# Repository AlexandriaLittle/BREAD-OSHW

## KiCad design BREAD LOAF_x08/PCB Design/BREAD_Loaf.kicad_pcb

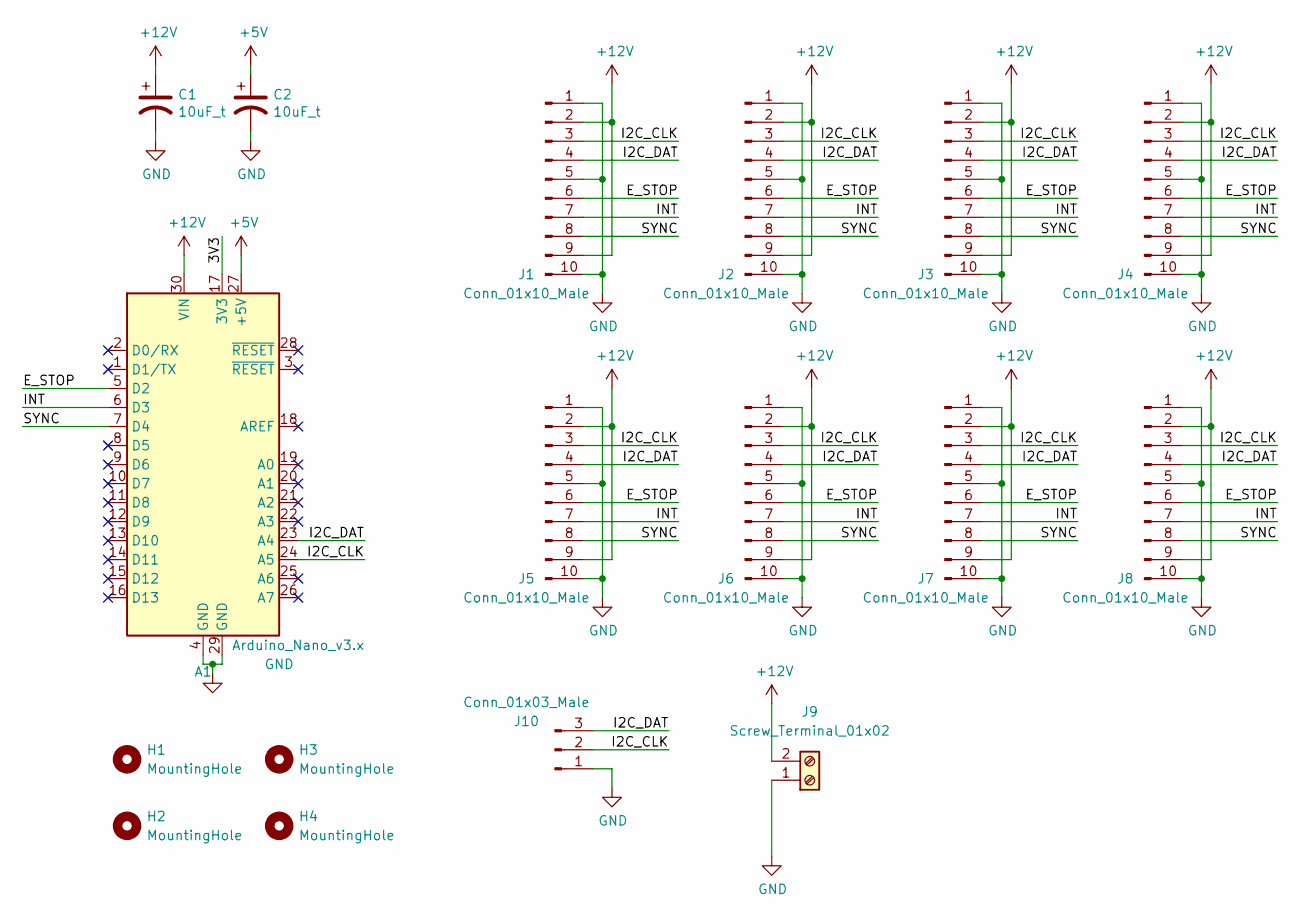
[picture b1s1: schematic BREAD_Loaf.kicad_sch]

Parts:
A1: Arduino_Nano_v3.x; Arduino_Nano
C1, C2: 10uF_t; C_1206_3216Metric_Pad1.33x1.80mm_HandSolder; Part # T491C106K025AT
H1, H2, H3, H4: MountingHole; MountingHole_3.2mm_M3_DIN965_Pad
J1, J2, J3, J4, J5, J6, J7, J8: Conn_01x10_Male; PinHeader_1x10_P2.54mm_Vertical
J9: Screw_Terminal_01x02; TerminalBlock_Phoenix_MKDS-1,5-2_1x02_P5.00mm_Horizontal
J10: Conn_01x03_Male; PinHeader_1x03_P2.54mm_Vertical

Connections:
+5V: A1.27 (+5V), C2.1
+12V: A1.30 (VIN), C1.1, J1.2, J1.9, J2.2, J2.9, J3.2, J3.9, J4.2, J4.9, J5.2, J5.9, J6.2, J6.9, J7.2, J7.9, J8.2, J8.9, J9.2
/3V3: A1.17 (3V3)
/E_STOP: A1.5 (D2), J1.6, J2.6, J3.6, J4.6, J5.6, J6.6, J7.6, J8.6
/I2C_CLK: A1.24 (A5), J1.3, J2.3, J3.3, J4.3, J5.3, J6.3, J7.3, J8.3, J10.2
/I2C_DAT: A1.23 (A4), J1.4, J2.4, J3.4, J4.4, J5.4, J6.4, J7.4, J8.4, J10.3
/INT: A1.6 (D3), J1.7, J2.7, J3.7, J4.7, J5.7, J6.7, J7.7, J8.7
/SYNC: A1.7 (D4), J1.8, J2.8, J3.8, J4.8, J5.8, J6.8, J7.8, J8.8
GND: A1.4 (GND), A1.29 (GND), C1.2, C2.2, J1.1, J1.5, J1.10, J2.1, J2.5, J2.10, J3.1, J3.5, J3.10, J4.1, J4.5, J4.10, J5.1, J5.5, J5.10, J6.1, J6.5, J6.10, J7.1, J7.5, J7.10, J8.1, J8.5, J8.10, J9.1, J10.1

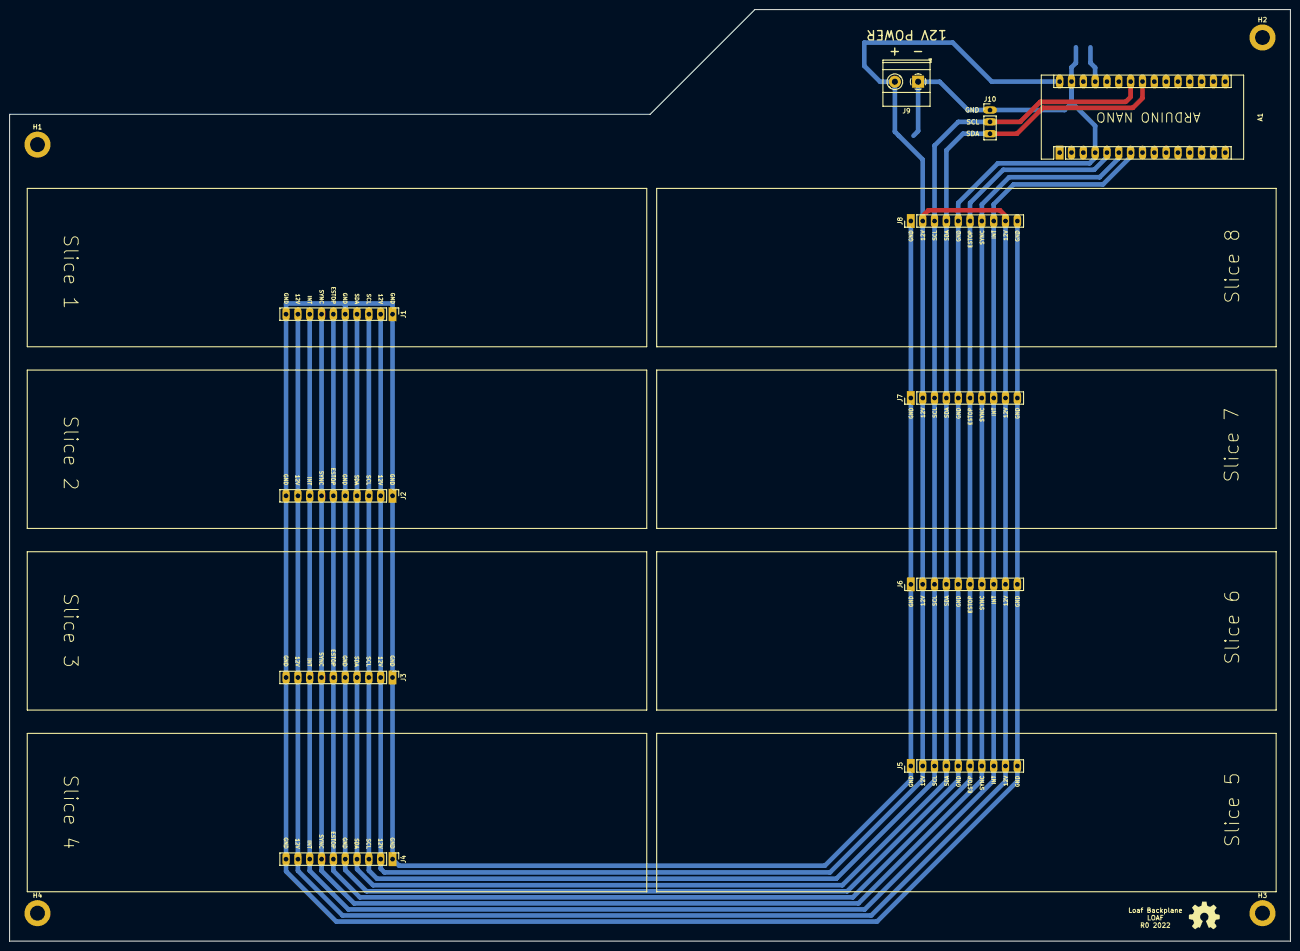
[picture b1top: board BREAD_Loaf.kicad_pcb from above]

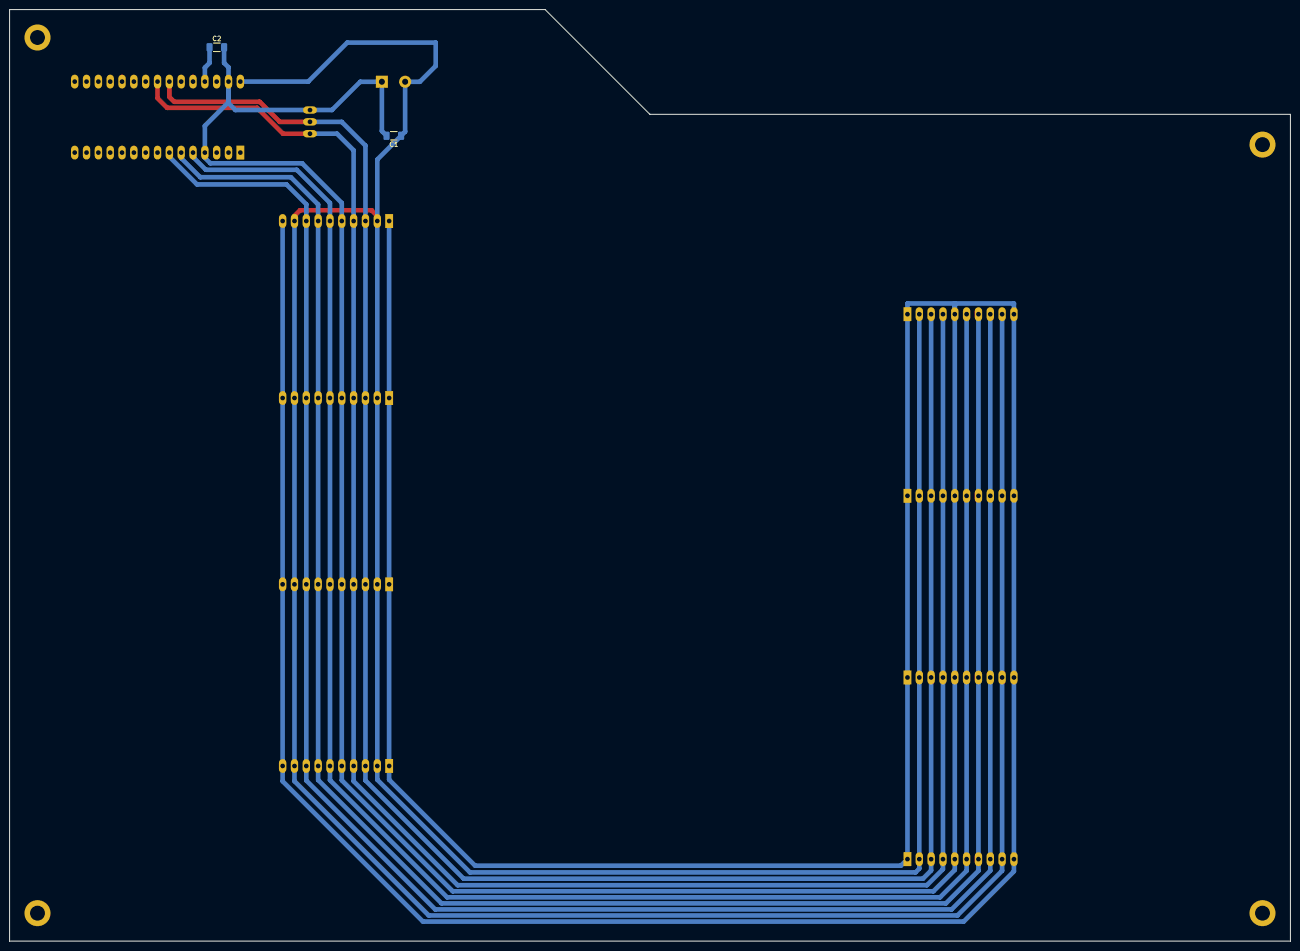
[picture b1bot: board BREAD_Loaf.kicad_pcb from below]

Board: 2 copper layers, 275.0 x 200.0 mm, 18 parts (2 on the bottom side), 8 nets.

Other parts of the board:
Logo1: Logo_Open_Hardware_Small; OSHW-Symbol_6.7x6mm_SilkScreen

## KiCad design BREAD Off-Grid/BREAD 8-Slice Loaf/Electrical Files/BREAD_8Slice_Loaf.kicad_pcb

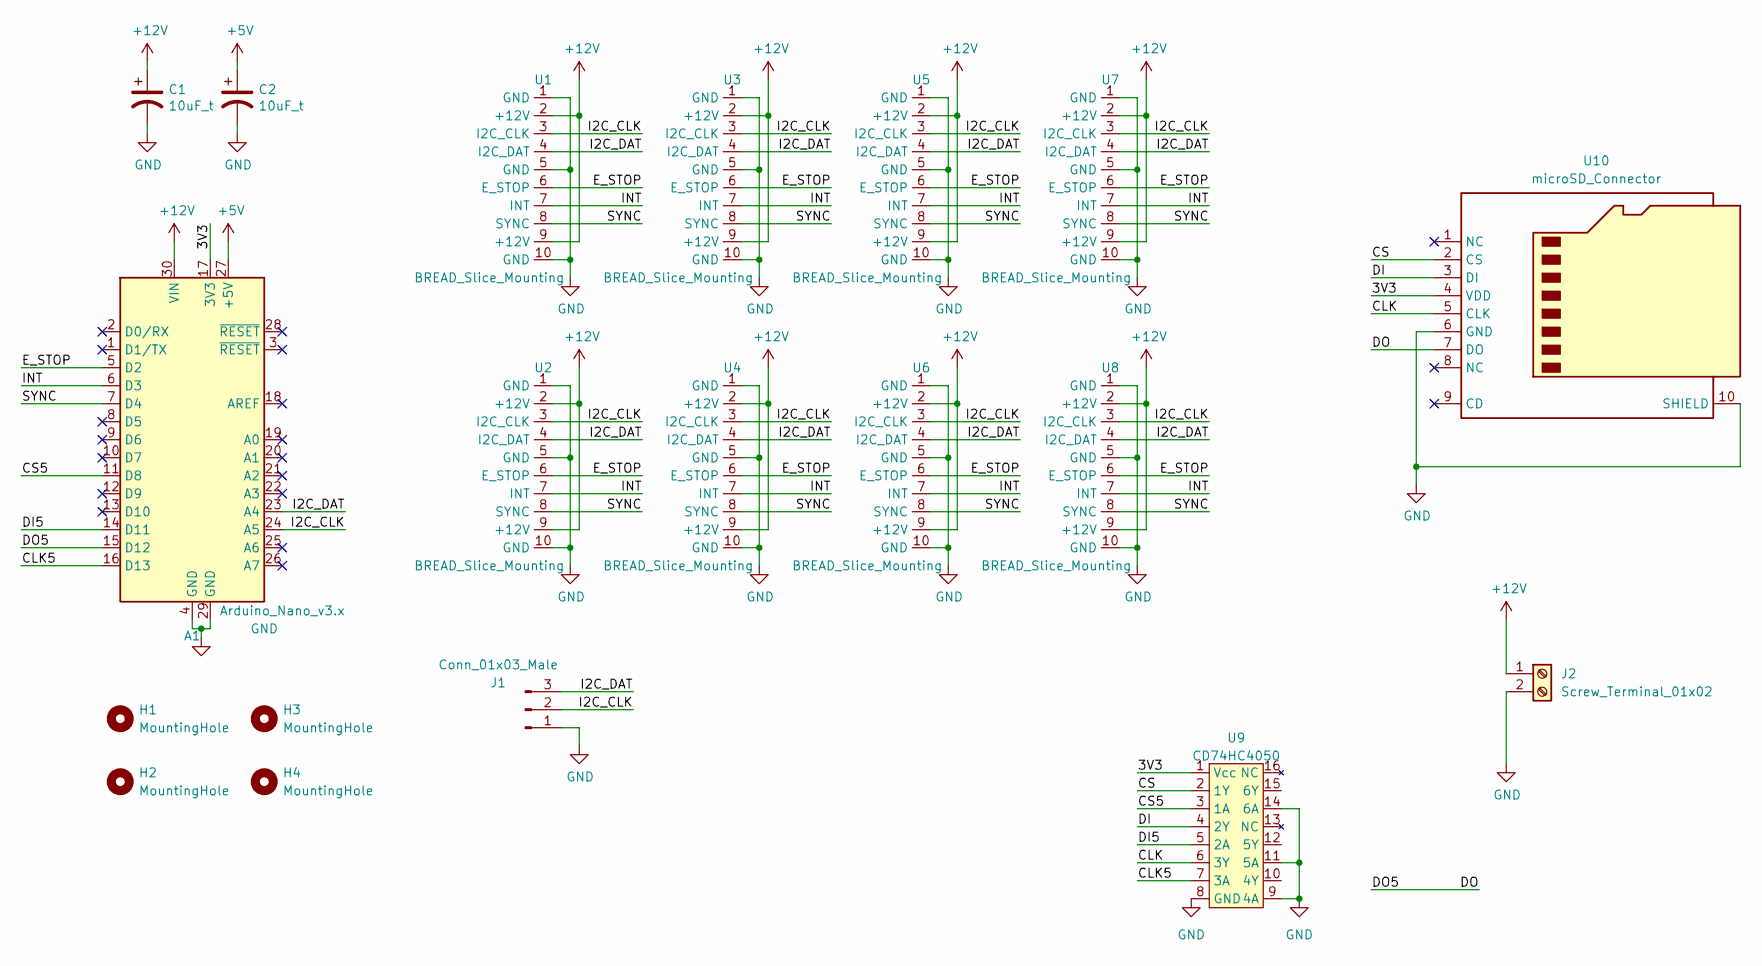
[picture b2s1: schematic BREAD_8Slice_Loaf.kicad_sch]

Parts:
A1: Arduino_Nano_v3.x; Arduino_Nano
C1, C2: 10uF_t; C_1206_3216Metric_Pad1.33x1.80mm_HandSolder; Part # T491C106K025AT
H1, H2, H3, H4: MountingHole; MountingHole_3.2mm_M3_DIN965_Pad
J1: Conn_01x03_Male; PinHeader_1x03_P2.54mm_Vertical
J2: Screw_Terminal_01x02; TerminalBlock_Phoenix_MKDS-1,5-2_1x02_P5.00mm_Horizontal
U1, U2, U3, U4, U5, U6, U7, U8: BREAD_Slice_Mounting
U9: CD74HC4050; DIP-16_W7.62mm_Socket_LongPads
U10: microSD_Connector; micro_SD_LOAF

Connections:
+5V: A1.27 (+5V), C2.1
+12V: A1.30 (VIN), C1.1, J2.1, U1.2 (+12V), U1.9 (+12V), U2.2 (+12V), U2.9 (+12V), U3.2 (+12V), U3.9 (+12V), U4.2 (+12V), U4.9 (+12V), U5.2 (+12V), U5.9 (+12V), U6.2 (+12V), U6.9 (+12V), U7.2 (+12V), U7.9 (+12V), U8.2 (+12V), U8.9 (+12V)
/3V3: A1.17 (3V3), U9.1 (Vcc), U10.4 (VDD)
/CLK: U9.6 (3Y), U10.5 (CLK)
/CLK5: A1.16 (D13), U9.7 (3A)
/CS: U9.2 (1Y), U10.2 (CS)
/CS5: A1.11 (D8), U9.3 (1A)
/DI: U9.4 (2Y), U10.3 (DI)
/DI5: A1.14 (D11), U9.5 (2A)
/DO: A1.15 (D12), U10.7 (DO)
/E_STOP: A1.5 (D2), U1.6 (E_STOP), U2.6 (E_STOP), U3.6 (E_STOP), U4.6 (E_STOP), U5.6 (E_STOP), U6.6 (E_STOP), U7.6 (E_STOP), U8.6 (E_STOP)
/I2C_CLK: A1.24 (A5), J1.2, U1.3 (I2C_CLK), U2.3 (I2C_CLK), U3.3 (I2C_CLK), U4.3 (I2C_CLK), U5.3 (I2C_CLK), U6.3 (I2C_CLK), U7.3 (I2C_CLK), U8.3 (I2C_CLK)
/I2C_DAT: A1.23 (A4), J1.3, U1.4 (I2C_DAT), U2.4 (I2C_DAT), U3.4 (I2C_DAT), U4.4 (I2C_DAT), U5.4 (I2C_DAT), U6.4 (I2C_DAT), U7.4 (I2C_DAT), U8.4 (I2C_DAT)
/INT: A1.6 (D3), U1.7 (INT), U2.7 (INT), U3.7 (INT), U4.7 (INT), U5.7 (INT), U6.7 (INT), U7.7 (INT), U8.7 (INT)
/SYNC: A1.7 (D4), U1.8 (SYNC), U2.8 (SYNC), U3.8 (SYNC), U4.8 (SYNC), U5.8 (SYNC), U6.8 (SYNC), U7.8 (SYNC), U8.8 (SYNC)
GND: A1.4 (GND), A1.29 (GND), C1.2, C2.2, J1.1, J2.2, U1.1 (GND), U1.5 (GND), U1.10 (GND), U2.1 (GND), U2.5 (GND), U2.10 (GND), U3.1 (GND), U3.5 (GND), U3.10 (GND), U4.1 (GND), U4.5 (GND), U4.10 (GND), U5.1 (GND), U5.5 (GND), U5.10 (GND), U6.1 (GND), U6.5 (GND), U6.10 (GND), U7.1 (GND), U7.5 (GND), U7.10 (GND), U8.1 (GND), U8.5 (GND), U8.10 (GND), U9.8 (GND), U9.9 (4A), U9.11 (5A), U9.14 (6A), U10.6 (GND), U10.10 (SHIELD)

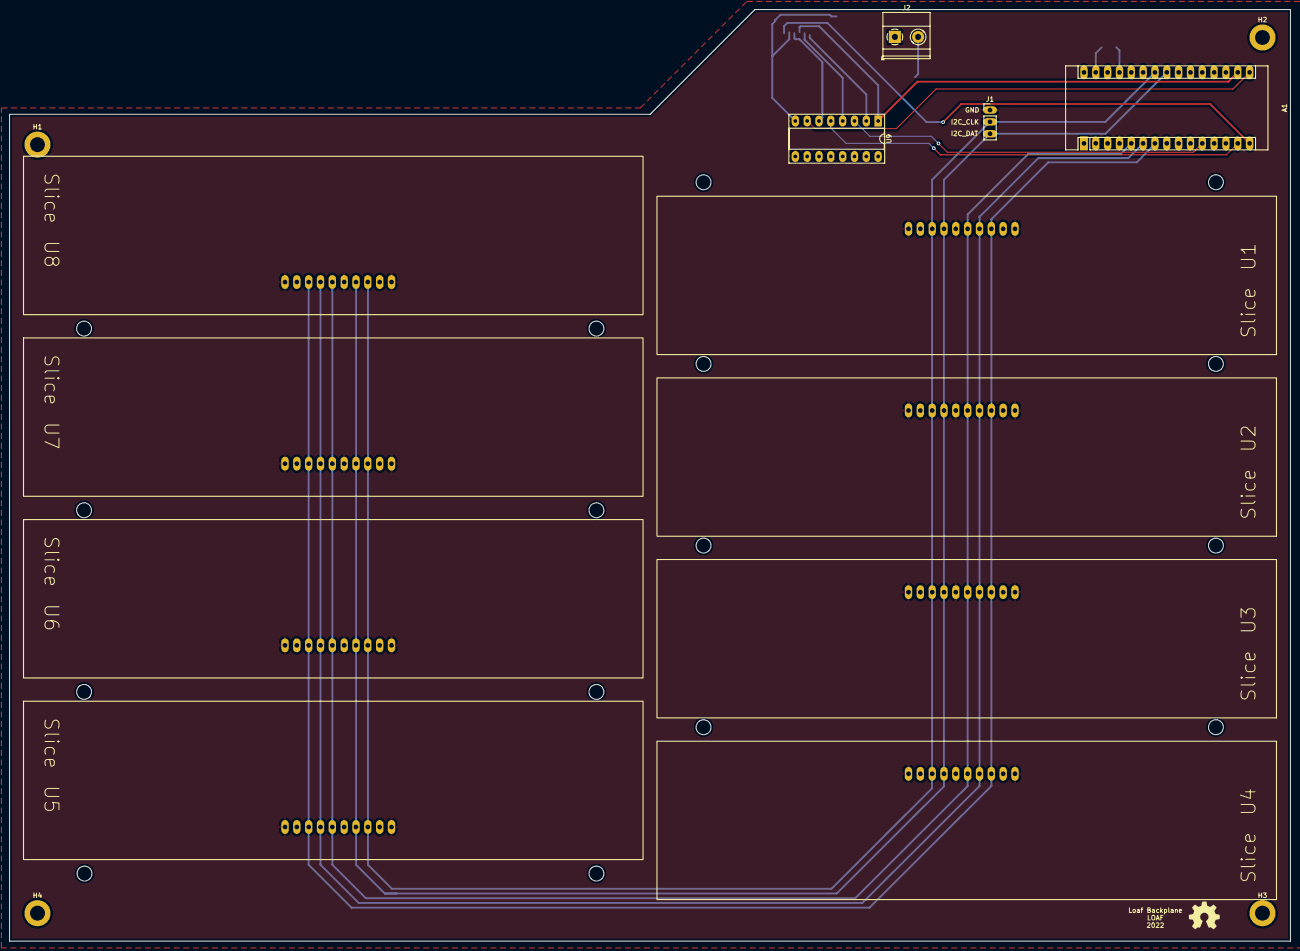
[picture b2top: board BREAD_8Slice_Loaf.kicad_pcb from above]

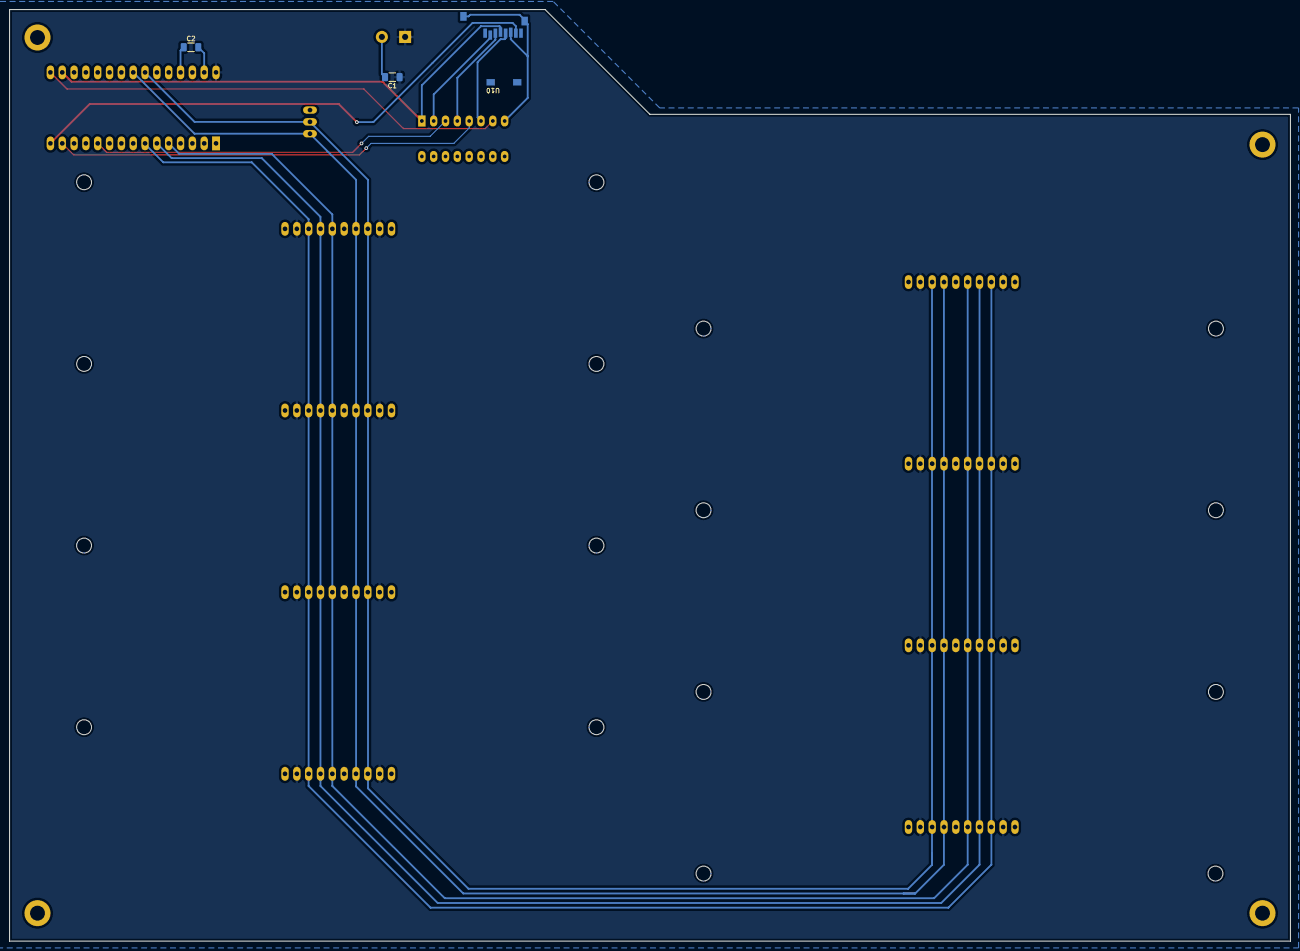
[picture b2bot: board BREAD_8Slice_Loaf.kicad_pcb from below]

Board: 2 copper layers, 275.0 x 200.0 mm, 20 parts (3 on the bottom side), 16 nets.

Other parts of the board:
Logo1: Logo_Open_Hardware_Small; OSHW-Symbol_6.7x6mm_SilkScreen

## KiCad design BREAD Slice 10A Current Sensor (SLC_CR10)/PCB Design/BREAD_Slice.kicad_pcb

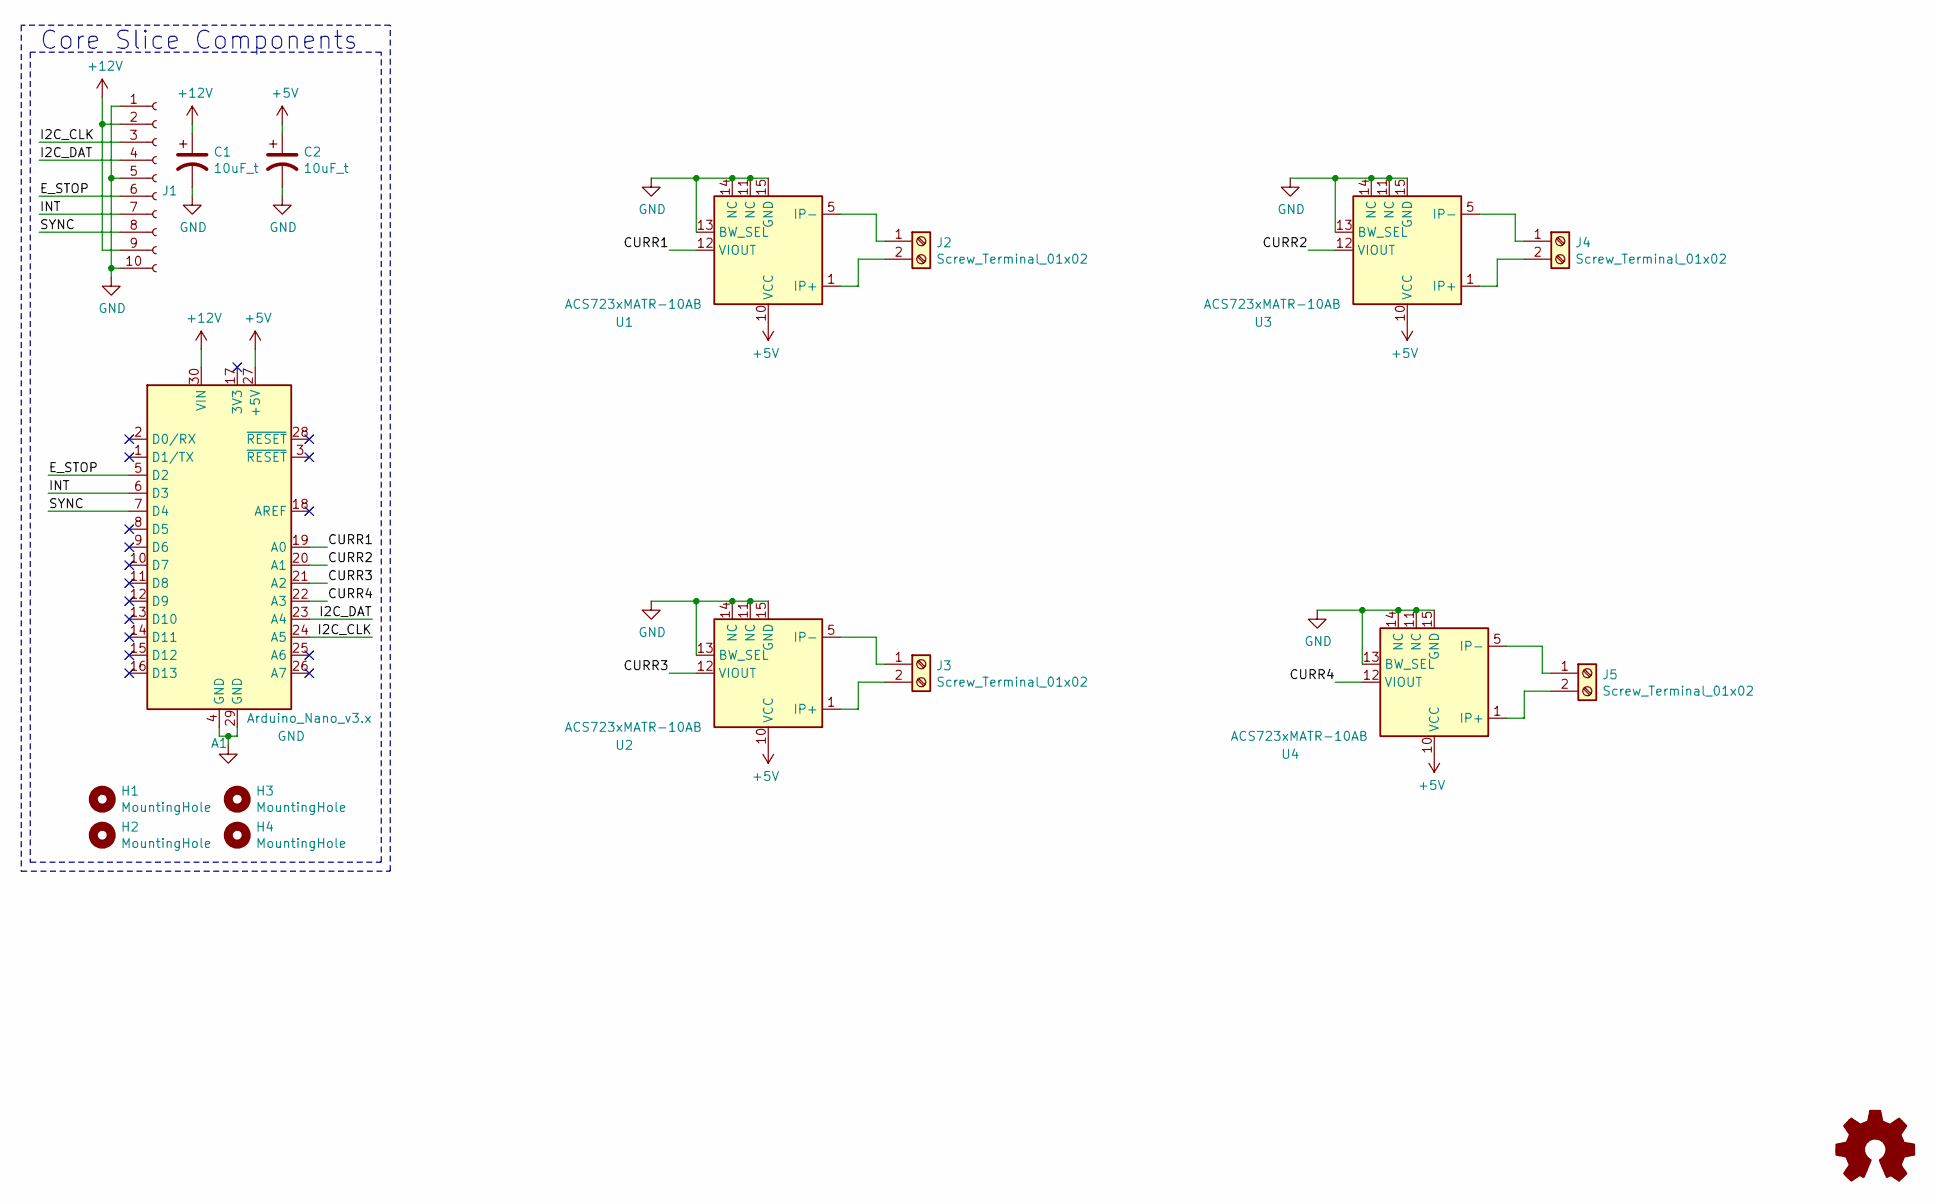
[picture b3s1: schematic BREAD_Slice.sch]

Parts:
A1: Arduino_Nano_v3.x; Arduino_Nano
C1, C2: 10uF_t; C_2312; Part # T491C106K025AT
H1, H2, H3, H4: MountingHole; MountingHole_3.2mm_M3_DIN965_Pad
J1: Conn_01x10_Female; PinSocket_1x10_P2.54mm_Horizontal
J2, J3, J4, J5: Screw_Terminal_01x02; TerminalBlock_TE_282834-2_1x02_P2.54mm_Horizontal
Logo1: Logo_Open_Hardware_Small; OSHW-Symbol_6.7x6mm_SilkScreen
U1, U2, U3, U4: ACS723xMATR-10AB; SOIC-16W_7.5x10.3mm_P1.27mm

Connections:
+5V: A1.27 (+5V), C2.1, U1.10 (VCC), U2.10 (VCC), U3.10 (VCC), U4.10 (VCC)
+12V: A1.30 (VIN), C1.1, J1.2, J1.9
/CURR1: A1.19 (A0), U1.12 (VIOUT)
/CURR2: A1.20 (A1), U3.12 (VIOUT)
/CURR3: A1.21 (A2), U2.12 (VIOUT)
/CURR4: A1.22 (A3), U4.12 (VIOUT)
/E_STOP: A1.5 (D2), J1.6
/I2C_CLK: A1.24 (A5), J1.3
/I2C_DAT: A1.23 (A4), J1.4
/INT: A1.6 (D3), J1.7
/SYNC: A1.7 (D4), J1.8
GND: A1.4 (GND), A1.29 (GND), C1.2, C2.2, J1.1, J1.5, J1.10, U1.11 (NC), U1.13 (BW_SEL), U1.14 (NC), U1.15 (GND), U2.11 (NC), U2.13 (BW_SEL), U2.14 (NC), U2.15 (GND), U3.11 (NC), U3.13 (BW_SEL), U3.14 (NC), U3.15 (GND), U4.11 (NC), U4.13 (BW_SEL), U4.14 (NC), U4.15 (GND)
unnamed: J2.1, U1.5 (IP-), U1.6 (IP-), U1.7 (IP-), U1.8 (IP-)
unnamed: J2.2, U1.1 (IP+), U1.2 (IP+), U1.3 (IP+), U1.4 (IP+)
unnamed: J3.1, U2.5 (IP-), U2.6 (IP-), U2.7 (IP-), U2.8 (IP-)
unnamed: J3.2, U2.1 (IP+), U2.2 (IP+), U2.3 (IP+), U2.4 (IP+)
unnamed: J4.1, U3.5 (IP-), U3.6 (IP-), U3.7 (IP-), U3.8 (IP-)
unnamed: J4.2, U3.1 (IP+), U3.2 (IP+), U3.3 (IP+), U3.4 (IP+)
unnamed: J5.1, U4.5 (IP-), U4.6 (IP-), U4.7 (IP-), U4.8 (IP-)
unnamed: J5.2, U4.1 (IP+), U4.2 (IP+), U4.3 (IP+), U4.4 (IP+)

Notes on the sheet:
Core Slice Components

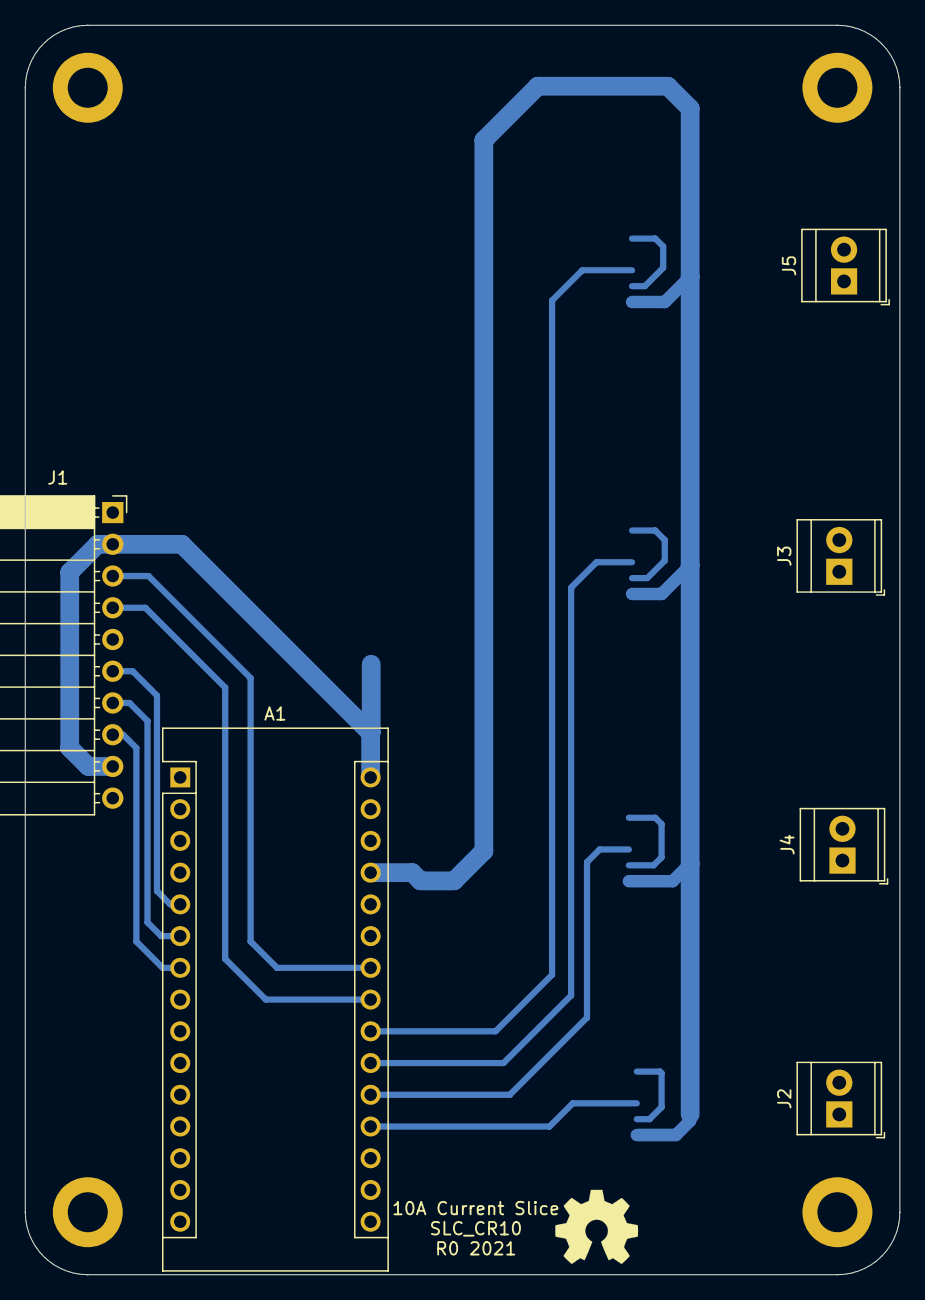
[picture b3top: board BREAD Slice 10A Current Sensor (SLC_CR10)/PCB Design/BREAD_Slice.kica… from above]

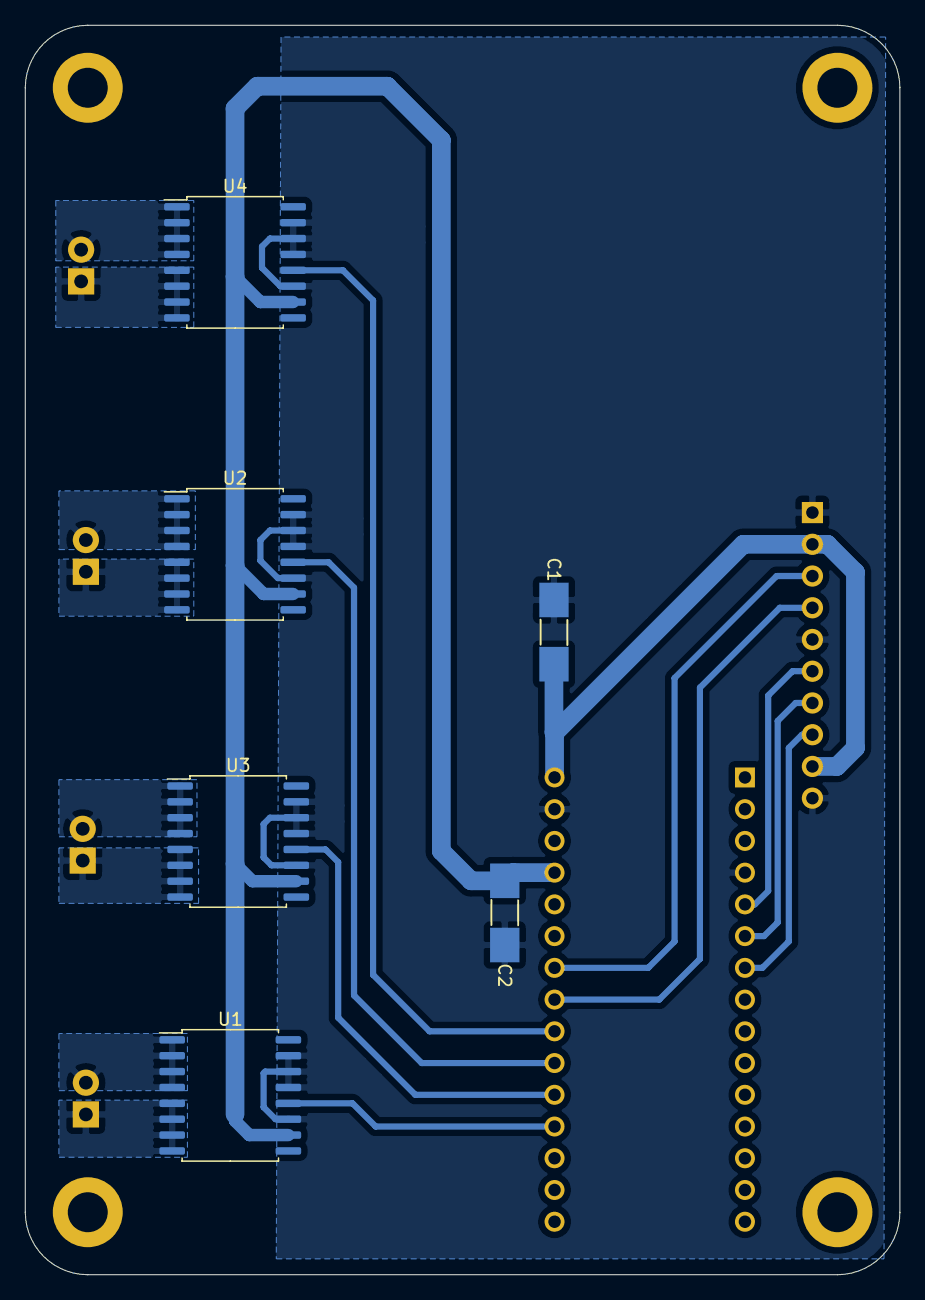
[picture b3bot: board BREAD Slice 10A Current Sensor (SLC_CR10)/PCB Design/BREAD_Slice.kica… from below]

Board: 2 copper layers, 70.0 x 100.0 mm, 17 parts (6 on the bottom side), 20 nets.

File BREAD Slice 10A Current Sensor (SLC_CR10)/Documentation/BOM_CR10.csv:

Id,Designator,Package,Quantity,Designation,Supplier and ref
1,"U4,U3,U2,U1",SOIC-16W_7.5x10.3mm_P1.27mm,4,ACS723xMATR-10AB,
2,"J5,J4,J3,J2",TerminalBlock_TE_282834-2_1x02_P2.54mm_Horizontal,4,Screw_Terminal_01x02,
3,Logo1,OSHW-Symbol_6.7x6mm_SilkScreen,1,Logo_Open_Hardware_Small,
4,"H4,H3,H2,H1",MountingHole_3.2mm_M3_DIN965_Pad,4,MountingHole,
5,"C1,C2",C_2312,2,10uF_t,
6,A1,Arduino_Nano,1,Arduino_Nano_v3.x,
7,J1,PinSocket_1x10_P2.54mm_Horizontal,1,Conn_01x10_Female,

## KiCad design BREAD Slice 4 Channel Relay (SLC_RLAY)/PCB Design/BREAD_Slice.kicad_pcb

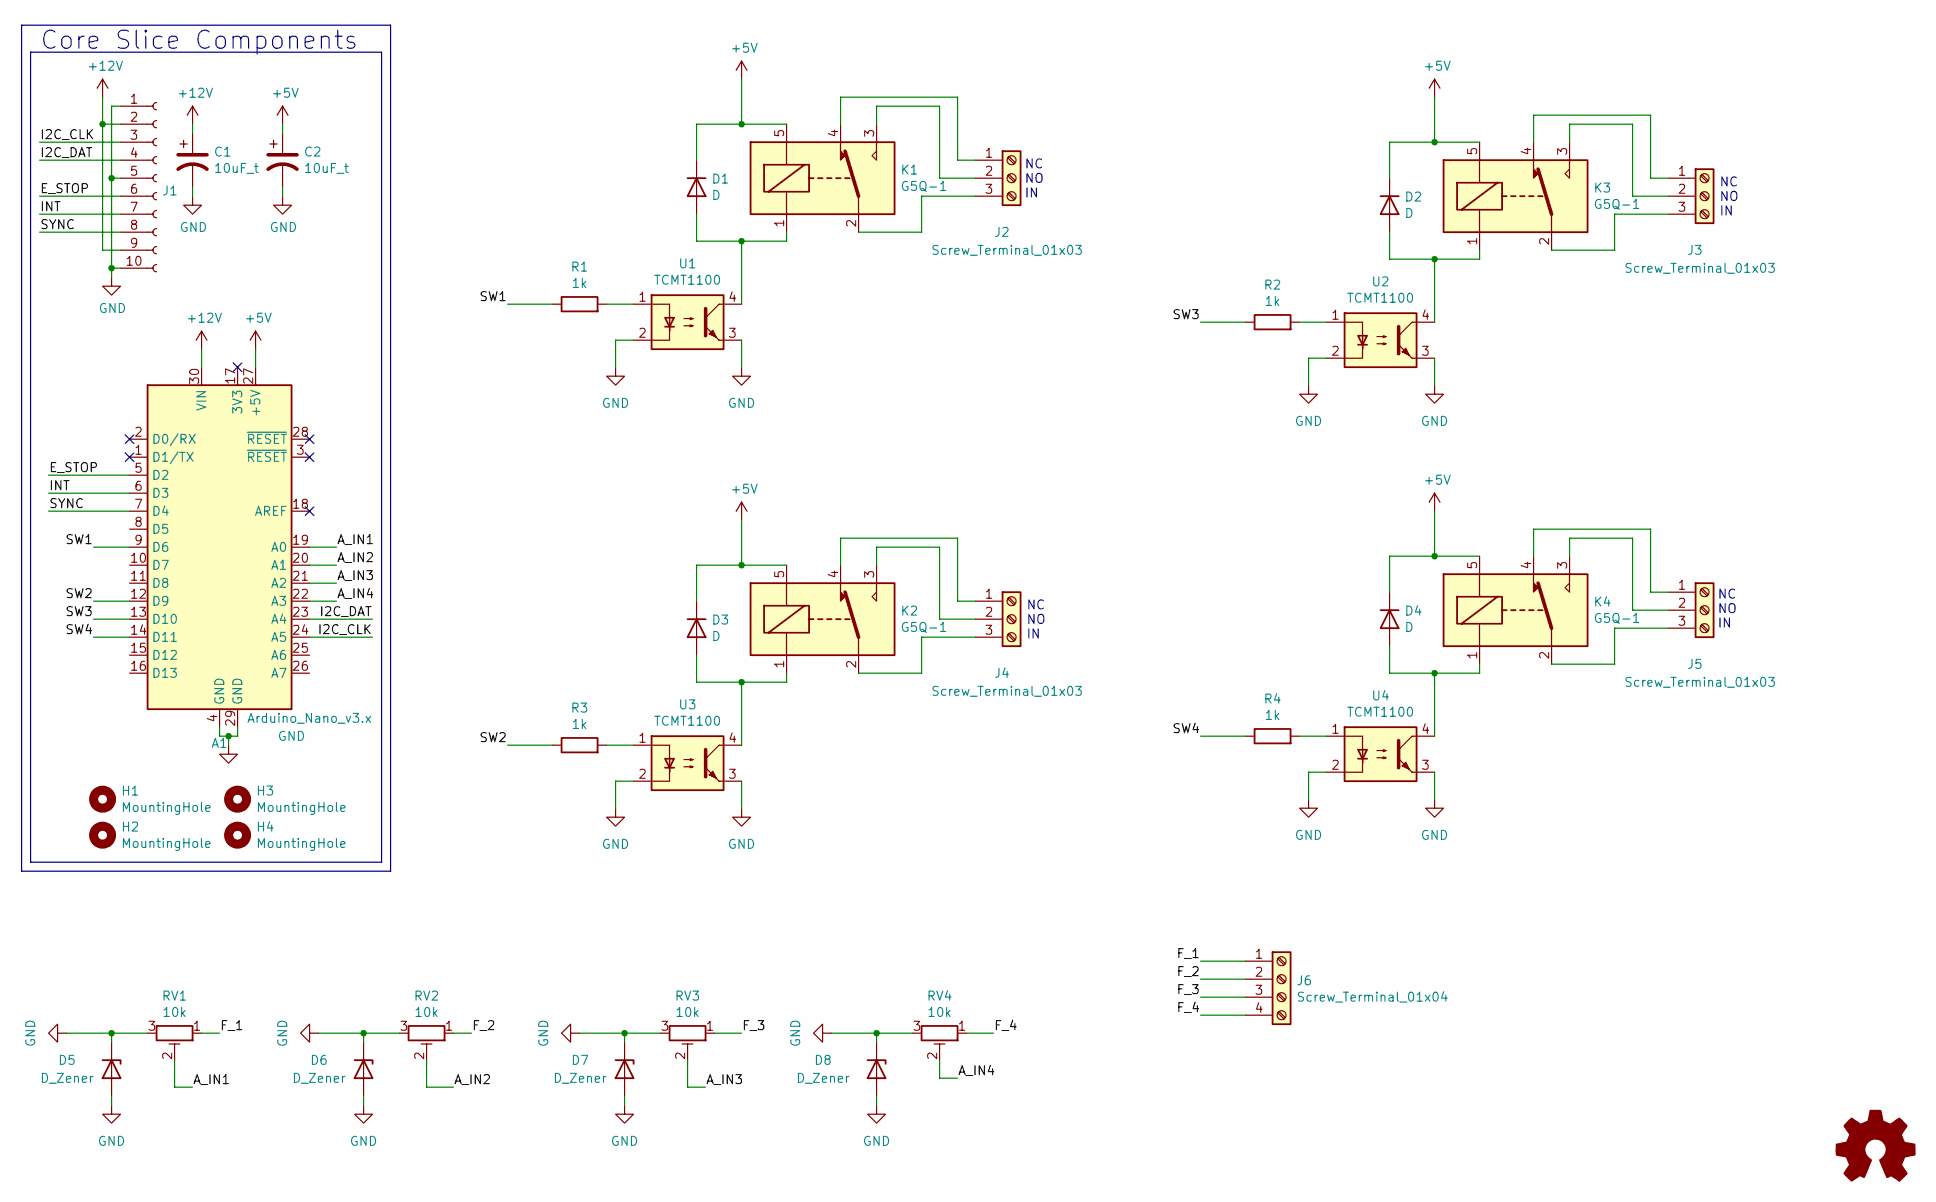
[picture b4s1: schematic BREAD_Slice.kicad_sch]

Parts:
A1: Arduino_Nano_v3.x; Arduino_Nano
C1, C2: 10uF_t; C_2312; Part # T491C106K025AT
D1, D2, D3, D4: D; D_1206_3216Metric_Pad1.42x1.75mm_HandSolder
D5, D6, D7, D8: D_Zener; D_1206_3216Metric_Pad1.42x1.75mm_HandSolder
H1, H2, H3, H4: MountingHole; MountingHole_3.2mm_M3_DIN965_Pad
J1: Conn_01x10_Female; PinSocket_1x10_P2.54mm_Horizontal
J2, J3, J4, J5: Screw_Terminal_01x03; TerminalBlock_TE_282834-3_1x03_P2.54mm_Horizontal
J6: Screw_Terminal_01x04; TerminalBlock_TE_282834-4_1x04_P2.54mm_Horizontal
K1, K2, K3, K4: G5Q-1; Relay_SPDT_Omron-G5Q-1
Logo1: Logo_Open_Hardware_Small; OSHW-Symbol_6.7x6mm_SilkScreen
R1, R2, R3, R4: 1k; R_1206_3216Metric_Pad1.30x1.75mm_HandSolder
RV1, RV2, RV3, RV4: 10k; Potentiometer_Bourns_3266W_Vertical
U1, U2, U3, U4: TCMT1100; SOP-4_4.4x2.6mm_P1.27mm

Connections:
+5V: A1.27 (+5V), C2.1, D1.1 (K), D2.1 (K), D3.1 (K), D4.1 (K), K1.5, K2.5, K3.5, K4.5
+12V: A1.30 (VIN), C1.1, J1.2, J1.9
/A_IN1: A1.19 (A0), RV1.2
/A_IN2: A1.20 (A1), RV2.2
/A_IN3: A1.21 (A2), RV3.2
/A_IN4: A1.22 (A3), RV4.2
/E_STOP: A1.5 (D2), J1.6
/F_1: J6.1, RV1.1
/F_2: J6.2, RV2.1
/F_3: J6.3, RV3.1
/F_4: J6.4, RV4.1
/I2C_CLK: A1.24 (A5), J1.3
/I2C_DAT: A1.23 (A4), J1.4
/INT: A1.6 (D3), J1.7
/SW1: A1.9 (D6), R1.1
/SW2: A1.12 (D9), R3.1
/SW3: A1.13 (D10), R2.1
/SW4: A1.14 (D11), R4.1
/SYNC: A1.7 (D4), J1.8
GND: A1.4 (GND), A1.29 (GND), C1.2, C2.2, D5.1 (K), D5.2 (A), D6.1 (K), D6.2 (A), D7.1 (K), D7.2 (A), D8.1 (K), D8.2 (A), J1.1, J1.5, J1.10, RV1.3, RV2.3, RV3.3, RV4.3, U1.2, U1.3, U2.2, U2.3, U3.2, U3.3, U4.2, U4.3
unnamed: D1.2 (A), K1.1, U1.4
unnamed: D2.2 (A), K3.1, U2.4
unnamed: D3.2 (A), K2.1, U3.4
unnamed: D4.2 (A), K4.1, U4.4
unnamed: J2.1, K1.4
unnamed: J2.2, K1.3
unnamed: J2.3, K1.2
unnamed: J3.1, K3.4
unnamed: J3.2, K3.3
unnamed: J3.3, K3.2
unnamed: J4.1, K2.4
unnamed: J4.2, K2.3
unnamed: J4.3, K2.2
unnamed: J5.1, K4.4
unnamed: J5.2, K4.3
unnamed: J5.3, K4.2
unnamed: R1.2, U1.1
unnamed: R2.2, U2.1
unnamed: R3.2, U3.1
unnamed: R4.2, U4.1

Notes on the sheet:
NC NO IN
Core Slice Components

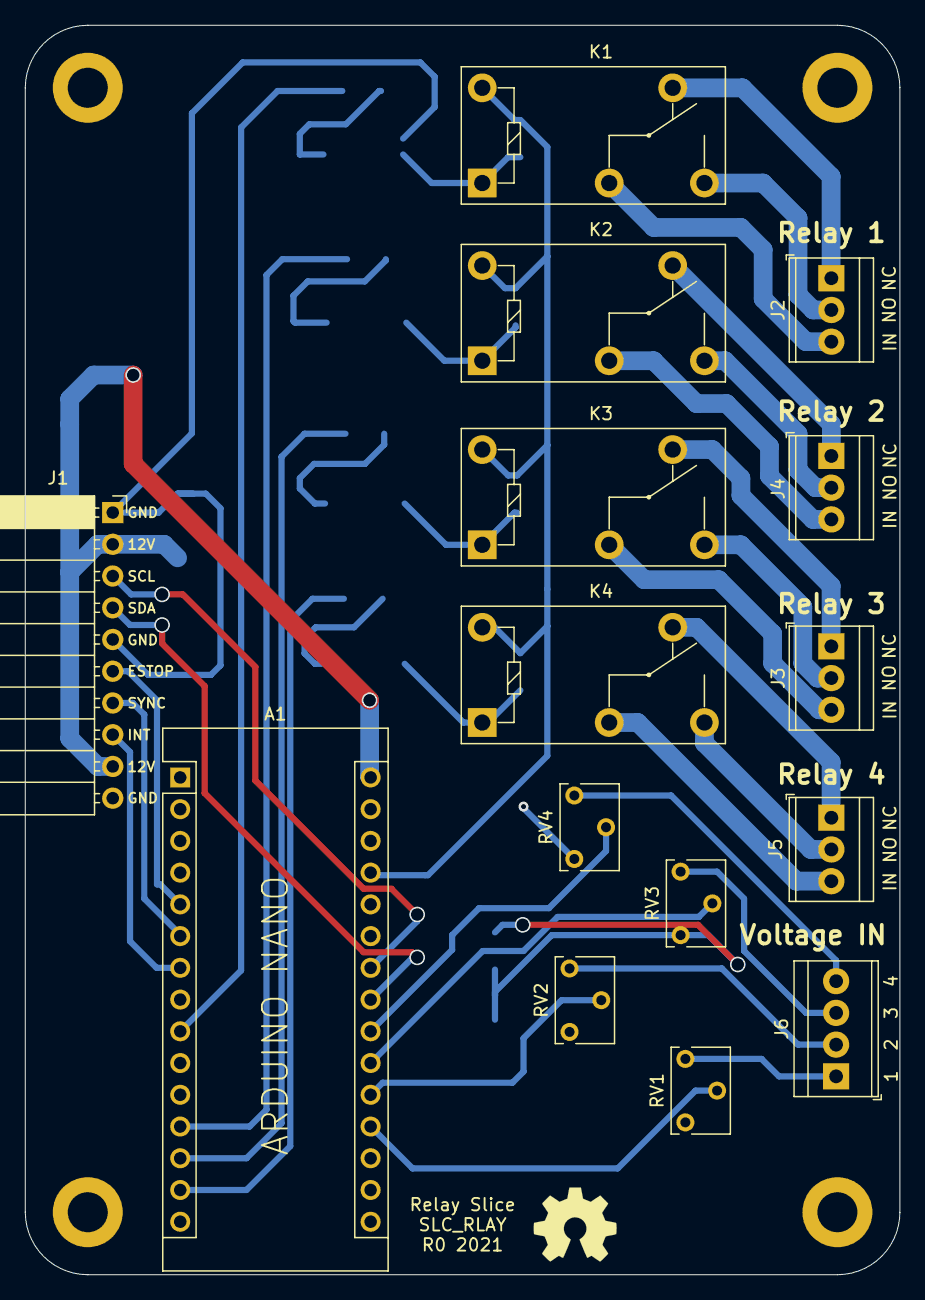
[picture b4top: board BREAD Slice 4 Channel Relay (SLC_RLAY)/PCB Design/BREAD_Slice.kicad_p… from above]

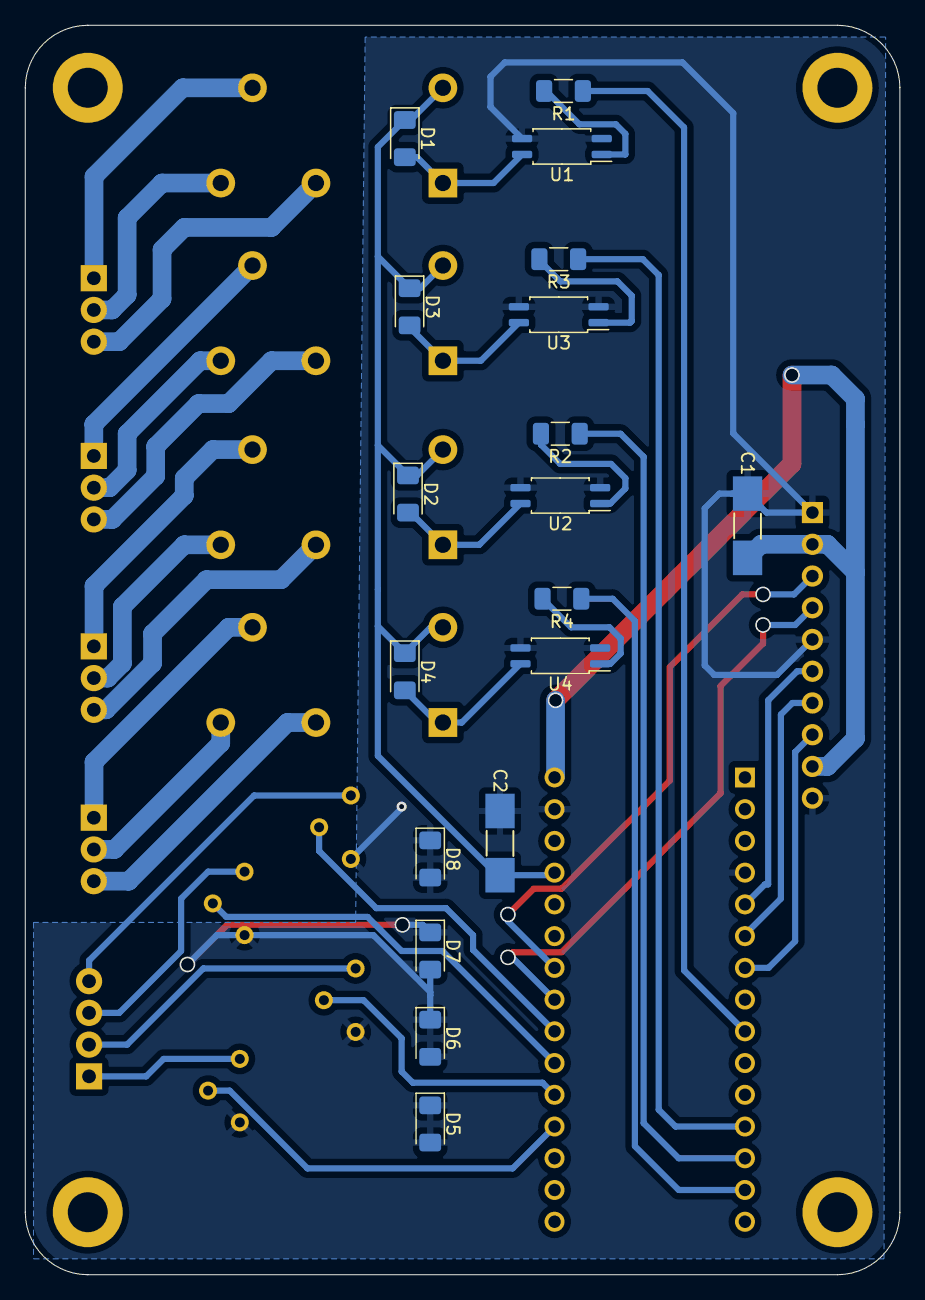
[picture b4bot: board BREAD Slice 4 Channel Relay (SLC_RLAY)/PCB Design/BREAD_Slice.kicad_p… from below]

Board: 2 copper layers, 70.0 x 100.0 mm, 38 parts (18 on the bottom side), 40 nets.

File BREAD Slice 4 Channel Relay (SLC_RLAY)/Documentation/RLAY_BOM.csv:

"Id";"Designator";"Package";"Quantity";"Designation";"Supplier and ref";
1;"U2,U4,U3,U1";"SOP-4_4.4x2.6mm_P1.27mm";4;"TCMT1100";;;
2;"RV4,RV3,RV2,RV1";"Potentiometer_Bourns_3266W_Vertical";4;"10k";;;
3;"R4,R3,R2,R1";"R_1206_3216Metric_Pad1.30x1.75mm_HandSolder";4;"1k";;;
4;"K4,K3,K2,K1";"Relay_SPDT_Omron-G5Q-1";4;"G5Q-1";;;
5;"J6";"TerminalBlock_TE_282834-4_1x04_P2.54mm_Horizontal";1;"Screw_Terminal_01x04";;;
6;"J5,J4,J3,J2";"TerminalBlock_TE_282834-3_1x03_P2.54mm_Horizontal";4;"Screw_Terminal_01x03";;;
7;"D8,D7,D6,D5";"D_1206_3216Metric_Pad1.42x1.75mm_HandSolder";4;"D_Zener";;;
8;"D4,D3,D2,D1";"D_1206_3216Metric_Pad1.42x1.75mm_HandSolder";4;"D";;;
9;"C2,C1";"C_2312";2;"10uF_t";;;
10;"Logo1";"OSHW-Symbol_6.7x6mm_SilkScreen";1;"Logo_Open_Hardware_Small";;;
11;"H4,H3,H2,H1";"MountingHole_3.2mm_M3_DIN965_Pad";4;"MountingHole";;;
12;"A1";"Arduino_Nano";1;"Arduino_Nano_v3.x";;;
13;"J1";"PinSocket_1x10_P2.54mm_Horizontal";1;"Conn_01x10_Female";;;
